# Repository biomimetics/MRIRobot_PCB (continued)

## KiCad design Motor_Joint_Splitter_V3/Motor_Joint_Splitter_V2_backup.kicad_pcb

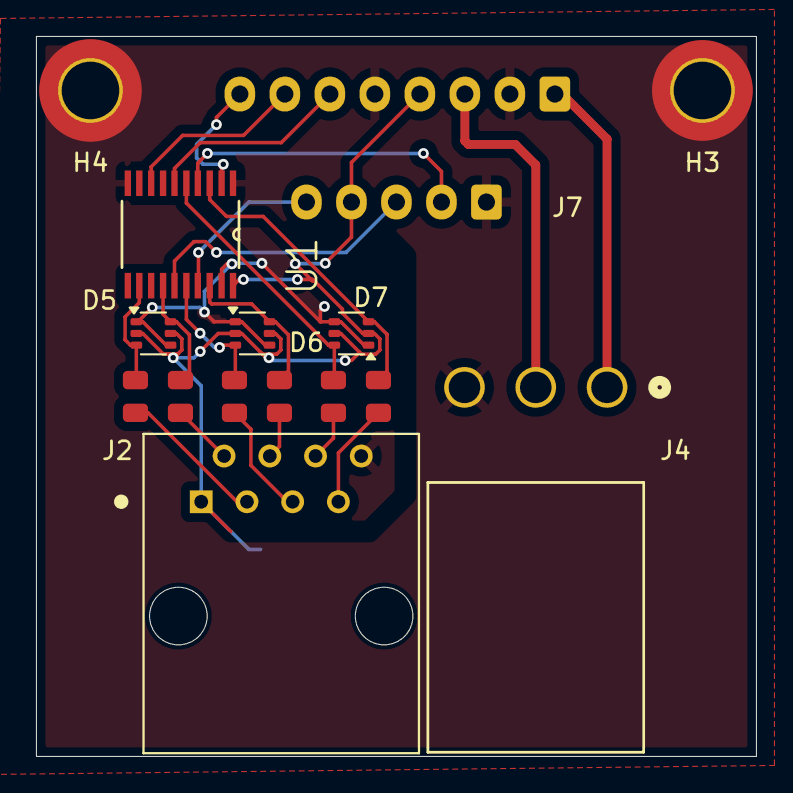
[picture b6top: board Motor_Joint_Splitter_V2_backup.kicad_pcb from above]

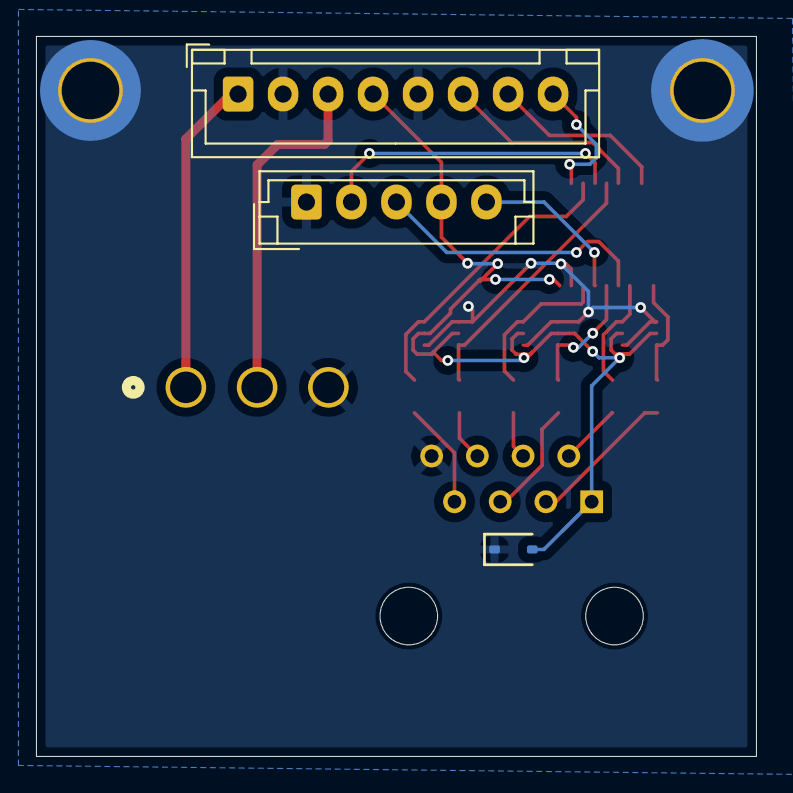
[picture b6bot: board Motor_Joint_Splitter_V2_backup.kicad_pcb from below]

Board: 2 copper layers, 40.0 x 40.0 mm, 17 parts (3 on the bottom side), 22 nets.

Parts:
D4: H5VHD3BC; D_SOD-323
D5, D6, D7: BAT54SDW; SOT-363_SC-70-6
H3: MountingHole_Pad; MountingHole_3.2mm_M3_DIN965_Pad_TopBottom
H4: MountingHole_Pad; MountingHole_3.2mm_M3_ISO7380_Pad_TopBottom
J1: Conn_01x08; JST_XH_B8B-XH-A_1x08_P2.50mm_Vertical
J2: 54602-908LF; AMPHENOL_54602-908LF
J4: 26605030; CONN_SDA-41792_M450_03_MOL
J7: Conn_01x05; JST_EH_B5B-EH-A_1x05_P2.50mm_Vertical
R13, R14, R15, R16, R17, R19: 120Ω; R_0805
U1: 74ACT244MTCX; SOP65P640X120-20N

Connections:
+5V: D4.2, D5.2 (K), D5.5 (K), D6.2 (K), D6.5 (K), D7.2 (K), D7.5 (K), J1.4, J2.1, J7.4, U1.20 (VCC)
/C_A: J1.6, U1.6 (I2)
/C_A_Out: D5.6 (K), R19.1, U1.14 (O2)
/C_A_Out_2: J2.2, R19.2
/C_B: J1.7, U1.8 (I3)
/C_B_Out: D5.3 (K), R13.1, U1.12 (O3)
/C_B_Out_2: J2.3, R13.2
/C_I: J1.8, U1.2 (I0)
/C_I_Out: D6.6 (K), R14.1, U1.18 (O0)
/C_I_Out_2: J2.4, R14.2
/Cos: J1.3, J4.2
/SEA_A: J7.3, U1.15 (I5)
/SEA_A_Out: D7.6 (A), R15.1, U1.5 (O5)
/SEA_A_Out_2: J2.6, R15.2
/SEA_B: J7.5, U1.17 (I4)
/SEA_B_Out: D7.3 (A), R16.1, U1.3 (O4)
/SEA_B_Out_2: J2.7, R16.2
/SEA_I: J7.2, U1.4 (I1)
/SEA_I_Out: D6.3 (A), R17.1, U1.16 (O1)
/SEA_I_Out_2: J2.5, R17.2
/Sin: J1.1, J4.1
GND: D4.1, D5.1 (A), D5.4 (A), D6.1 (A), D6.4 (A), D7.1 (A), D7.4 (A), H3.1, H4.1, J1.2, J1.5, J2.8, J4.3, J7.1, U1.1 (~OE1), U1.10 (GND), U1.19 (~OE2)
